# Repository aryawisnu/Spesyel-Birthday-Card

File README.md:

## Spesyel-Birthday-Card  
Giv this card to spesyel person that u have  
if u doesnt have spesyel person, dont be sad  
NOTE: suicide is bad idea wkwk :v 
>Component list
```
- Attiny85 SMD
- WS2812b RGB led
- Microphone 9767
- OLED display 0.96"
- CR2032 battery holder
- MSS22D18 Toggle Switch
- MTL1230 piezo SMD
- bunch of resistor
```
>Upload program to de board
````
1. u need arduino to do this
2. flash the arduino using arduinoISP program
3. install attinycore board by SpenceKonde
4. connect the arduino and the board using spi 6 pin port behind the oled
5. select the coreect board and port
6. compile and upload
````

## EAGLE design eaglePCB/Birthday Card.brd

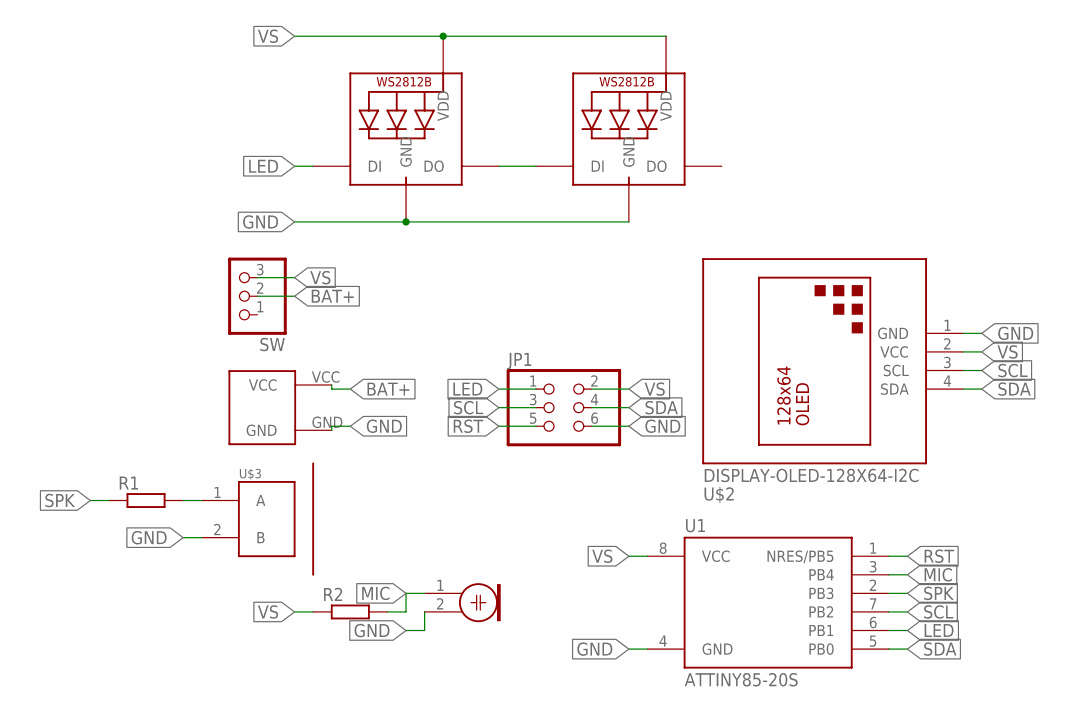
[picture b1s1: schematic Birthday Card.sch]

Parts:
JP1: PINHD-2X3; 2X03
LED1, LED2: WS2812B5050; WS2812B
M1: ELECTRET_MICROPHON-F6050AP; F6050AP
R1, R2: R-EU_R1206; R1206
SW: PINHD-1X3; 1X03
U1: ATTINY85-20S; SOIC8_EIAJ_208MIL
U$1: CR2032; CR2032-20MM
U$2: DISPLAY-OLED-128X64-I2C
U$3: PKLCS1212E2400-R1; BUZZ_PIEZO_SMD

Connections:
BAT+: SW.2, U$1.VCC
GND: JP1.6, LED1.3-GND (GND), LED2.3-GND (GND), M1.2, U1.4 (GND), U$1.GND, U$2.1 (GND), U$3.2 (B)
LED: JP1.1, LED1.4-DIN (DI), U1.6 (PB1)
MIC: M1.1, R2.2, U1.3 (PB4)
unnamed: LED1.2-DOUT (DO), LED2.4-DIN (DI)
unnamed: R1.2, U$3.1 (A)
RST: JP1.5, U1.1 (NRES/PB5)
SCL: JP1.3, U1.7 (PB2), U$2.3 (SCL)
SDA: JP1.4, U1.5 (PB0), U$2.4 (SDA)
SPK: R1.1, U1.2 (PB3)
VS: JP1.2, LED1.1-VDD (VDD), LED2.1-VDD (VDD), R2.1, SW.3, U1.8 (VCC), U$2.2 (VCC)

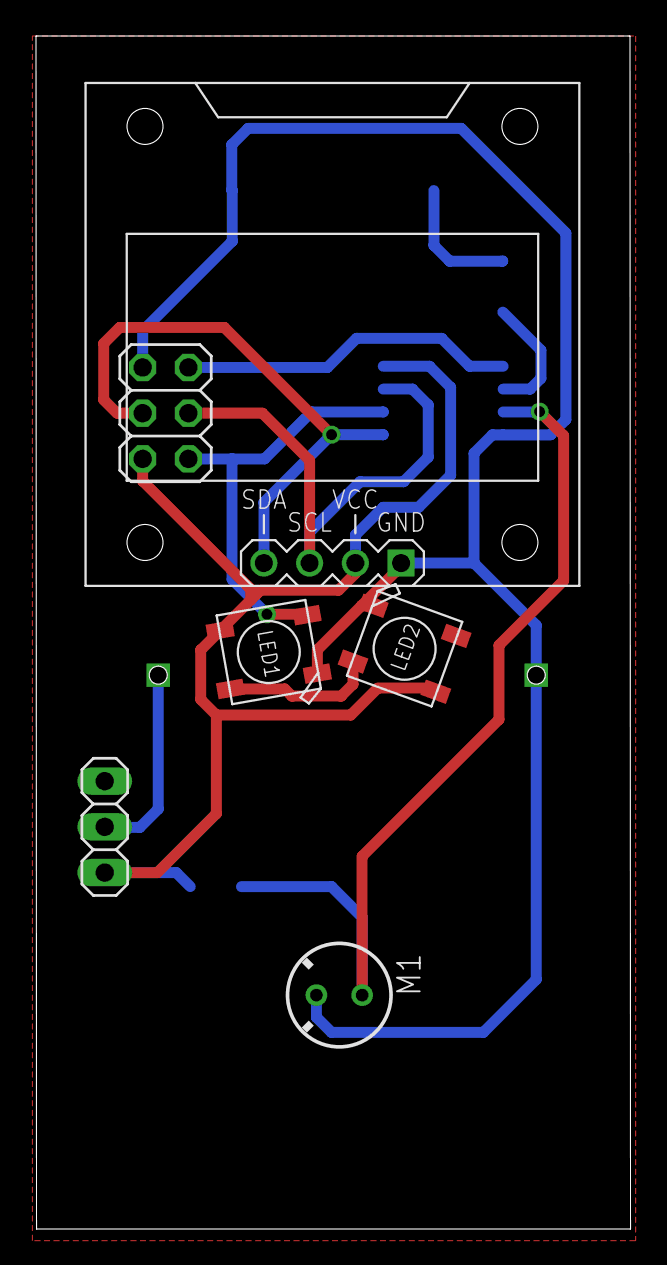
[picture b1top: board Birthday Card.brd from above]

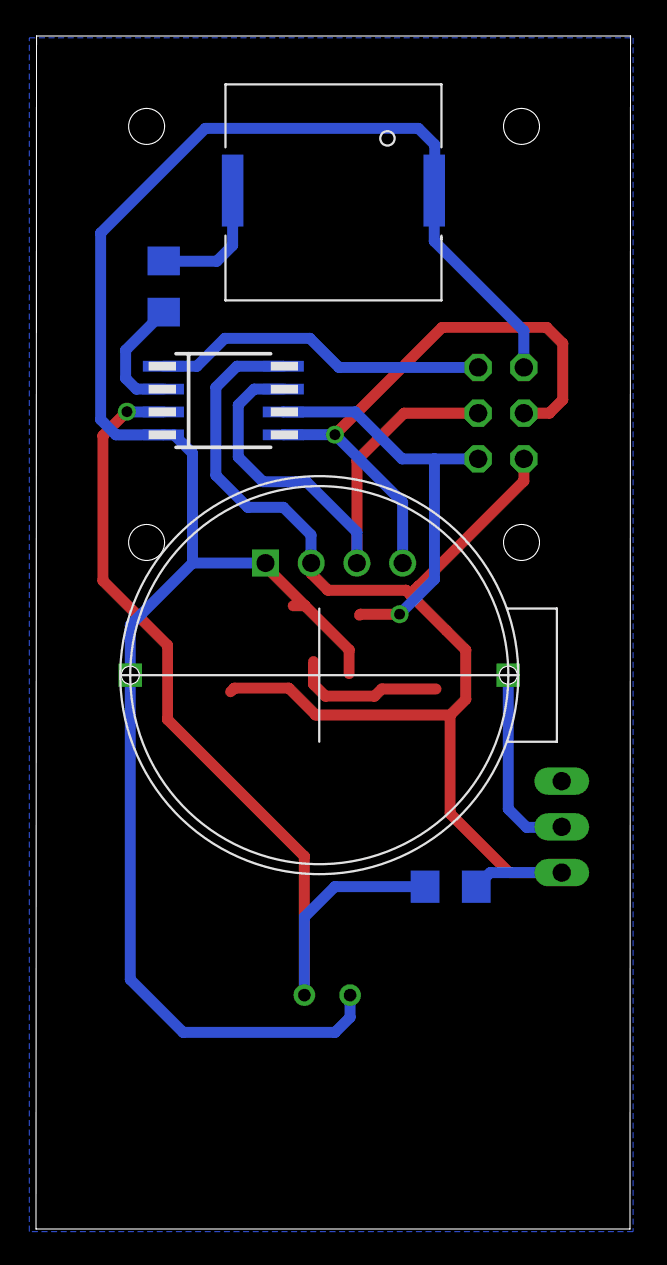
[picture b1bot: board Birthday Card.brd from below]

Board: 2 copper layers, 33.0 x 66.3 mm, 11 parts (5 on the bottom side), 11 nets.

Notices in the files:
parts and their libraries:
diy-modules: Released under the Creative Commons Attribution 4.0 International License: http://creativecommons.org/licenses/by/4.0
